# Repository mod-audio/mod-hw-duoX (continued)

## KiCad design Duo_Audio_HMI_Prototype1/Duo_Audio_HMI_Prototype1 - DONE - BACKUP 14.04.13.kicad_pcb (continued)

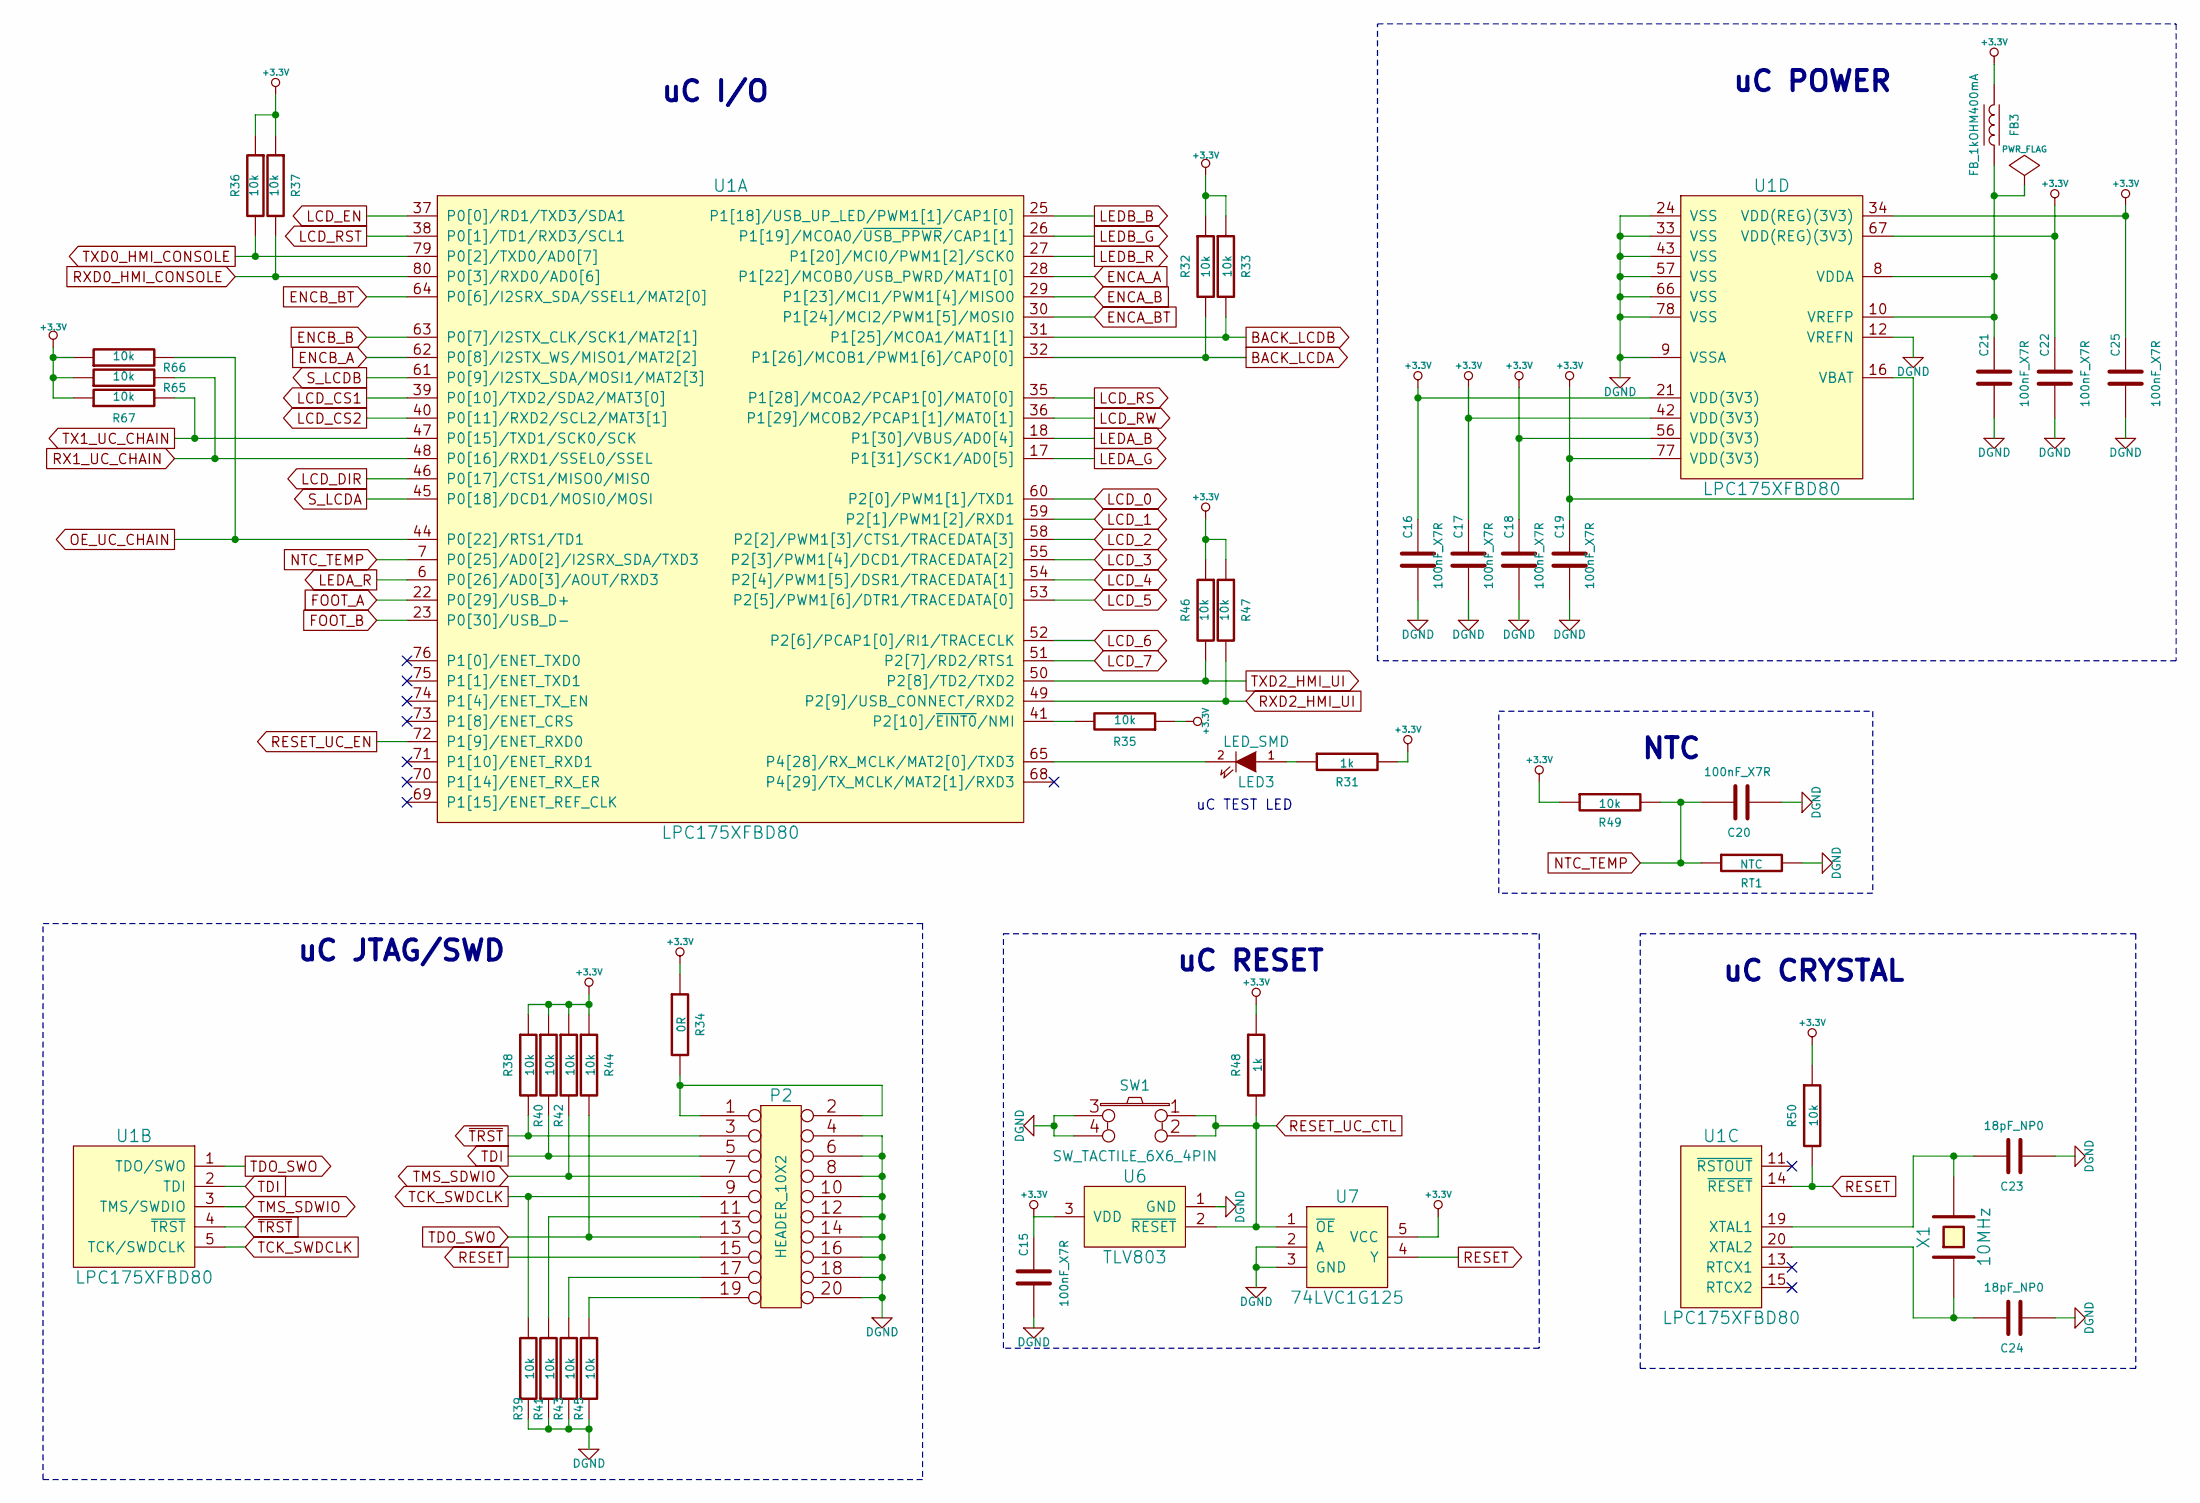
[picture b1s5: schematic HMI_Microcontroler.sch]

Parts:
C15, C16, C17, C18, C19, C20, C21, C22, C25: 100nF_X7R; SM0603
C23, C24: 18pF_NP0; SM0603
FB3: FB_1kOHM400mA; SM0805
LED3: LED_SMD; SM0805
P2: HEADER_10X2; PIN_ARRAY_2X10
R31, R48: 1k; SM0603
R32, R33, R35, R36, R37, R38, R39, R40, R41, R42, R43, R44, R45, R46, R47, R49, R50, R65, R66, R67: 10k; SM0603
R34: 0R; SM0805
RT1: NTC; SM0805
SW1: SW_TACTILE_6X6_4PIN; TACTILE_SWITCH_6x6
U1: LPC175XFBD80; LQFP80
U6: TLV803; SOT23
U7: 74LVC1G125; SOT353
X1: 10MHz; HC_49US

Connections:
+3.3V: C15.1, C16.1, C17.1, C18.1, C19.1, C22.1, C25.1, FB3.1, R31.2, R32.1, R33.1, R34.1, R35.1, R36.1, R37.1, R38.1, R40.1, R42.1, R44.1, R46.1, R47.1, R48.1, R49.1, R50.1, R65.1, R66.1, R67.1, U1.16 (VBAT), U1.21 (VDD(3V3)), U1.34 (VDD(REG)(3V3)), U1.42 (VDD(3V3)), U1.56 (VDD(3V3)), U1.67 (VDD(REG)(3V3)), U1.77 (VDD(3V3)), U6.3 (VDD), U7.5 (VCC); also elsewhere on the board
AGND: C15.2, C16.2, C17.2, C18.2, C19.2, C20.2, C21.2, C22.2, C23.2, C24.2, C25.2, P2.4, P2.6, P2.8, P2.10, P2.12, P2.14, P2.16, P2.18, P2.20, R39.1, R41.1, R43.1, R45.1, RT1.2, SW1.3, SW1.4, U1.9 (VSSA), U1.12 (VREFN), U1.24 (VSS), U1.33 (VSS), U1.43 (VSS), U1.57 (VSS), U1.66 (VSS), U1.78 (VSS), U6.1 (GND), U7.2 (A), U7.3 (GND); also elsewhere on the board
BACK_LCDA: R32.2, U1.32 (P1[26]/MCOB1/PWM1[6]/CAP0[0]); also elsewhere on the board
BACK_LCDB: R33.2, U1.31 (P1[25]/MCOA1/MAT1[1]); also elsewhere on the board
ENCA_A: U1.28 (P1[22]/MCOB0/USB_PWRD/MAT1[0]); also elsewhere on the board
ENCA_B: U1.29 (P1[23]/MCI1/PWM1[4]/MISO0); also elsewhere on the board
ENCA_BT: U1.30 (P1[24]/MCI2/PWM1[5]/MOSI0); also elsewhere on the board
ENCB_A: U1.62 (P0[8]/I2STX_WS/MISO1/MAT2[2]); also elsewhere on the board
ENCB_B: U1.63 (P0[7]/I2STX_CLK/SCK1/MAT2[1]); also elsewhere on the board
ENCB_BT: U1.64 (P0[6]/I2SRX_SDA/SSEL1/MAT2[0]); also elsewhere on the board
FOOT_A: U1.22 (P0[29]/USB_D+); also elsewhere on the board
FOOT_B: U1.23 (P0[30]/USB_D-); also elsewhere on the board
LCD_0: U1.60 (P2[0]/PWM1[1]/TXD1); also elsewhere on the board
LCD_1: U1.59 (P2[1]/PWM1[2]/RXD1); also elsewhere on the board
LCD_2: U1.58 (P2[2]/PWM1[3]/CTS1/TRACEDATA[3]); also elsewhere on the board
LCD_3: U1.55 (P2[3]/PWM1[4]/DCD1/TRACEDATA[2]); also elsewhere on the board
LCD_4: U1.54 (P2[4]/PWM1[5]/DSR1/TRACEDATA[1]); also elsewhere on the board
LCD_5: U1.53 (P2[5]/PWM1[6]/DTR1/TRACEDATA[0]); also elsewhere on the board
LCD_6: U1.52 (P2[6]/PCAP1[0]/RI1/TRACECLK); also elsewhere on the board
LCD_7: U1.51 (P2[7]/RD2/RTS1); also elsewhere on the board
LCD_CS1: U1.39 (P0[10]/TXD2/SDA2/MAT3[0]); also elsewhere on the board
LCD_CS2: U1.40 (P0[11]/RXD2/SCL2/MAT3[1]); also elsewhere on the board
LCD_DIR: U1.46 (P0[17]/CTS1/MISO0/MISO); also elsewhere on the board
LCD_EN: U1.37 (P0[0]/RD1/TXD3/SDA1); also elsewhere on the board
LCD_RS: U1.35 (P1[28]/MCOA2/PCAP1[0]/MAT0[0]); also elsewhere on the board
LCD_RST: U1.38 (P0[1]/TD1/RXD3/SCL1); also elsewhere on the board
LCD_RW: U1.36 (P1[29]/MCOB2/PCAP1[1]/MAT0[1]); also elsewhere on the board
LEDA_B: U1.18 (P1[30]/VBUS/AD0[4]); also elsewhere on the board
LEDA_G: U1.17 (P1[31]/SCK1/AD0[5]); also elsewhere on the board
LEDA_R: U1.6 (P0[26]/AD0[3]/AOUT/RXD3); also elsewhere on the board
LEDB_B: U1.25 (P1[18]/USB_UP_LED/PWM1[1]/CAP1[0]); also elsewhere on the board
LEDB_G: U1.26 (P1[19]/MCOA0/~USB_PPWR~/CAP1[1]); also elsewhere on the board
LEDB_R: U1.27 (P1[20]/MCI0/PWM1[2]/SCK0); also elsewhere on the board
unnamed: LED3.1 (A), R31.1
unnamed: LED3.2 (K), U1.65 (P4[28]/RX_MCLK/MAT2[0]/TXD3)
unnamed: R35.2, U1.41 (P2[10]/~EINT0~/NMI)
unnamed: C21.1, FB3.2, U1.8 (VDDA), U1.10 (VREFP)
unnamed: C23.1, U1.19 (XTAL1), X1.2
unnamed: C24.1, U1.20 (XTAL2), X1.1
unnamed: P2.11, R41.2
unnamed: P2.1, P2.2, R34.2
unnamed: P2.17, R43.2
unnamed: P2.19, R45.2
NTC_TEMP: C20.1, R49.2, RT1.1, U1.7 (P0[25]/AD0[2]/I2SRX_SDA/TXD3)
OE_UC_CHAIN: R66.2, U1.44 (P0[22]/RTS1/TD1); also elsewhere on the board
RESET: P2.15, R50.2, U1.14 (~RESET), U7.4 (Y)
RESET_UC_CTL: R48.2, SW1.1, SW1.2, U6.2 (~RESET), U7.1 (~OE); also elsewhere on the board
RESET_UC_EN: U1.72 (P1[9]/ENET_RXD0); also elsewhere on the board
RX1_UC_CHAIN: R65.2, U1.48 (P0[16]/RXD1/SSEL0/SSEL); also elsewhere on the board
RXD0_HMI_CONSOLE: R37.2, U1.80 (P0[3]/RXD0/AD0[6]); also elsewhere on the board
RXD2_HMI_UI: R47.2, U1.49 (P2[9]/USB_CONNECT/RXD2); also elsewhere on the board
S_LCDA: U1.45 (P0[18]/DCD1/MOSI0/MOSI); also elsewhere on the board
S_LCDB: U1.61 (P0[9]/I2STX_SDA/MOSI1/MAT2[3]); also elsewhere on the board
TCK_SWDCLK: P2.9, R39.2, U1.5 (TCK/SWDCLK)
TDI: P2.5, R40.2, U1.2 (TDI)
TDO_SWO: P2.13, R44.2, U1.1 (TDO/SWO)
TMS_SDWIO: P2.7, R42.2, U1.3 (TMS/SWDIO)
TX1_UC_CHAIN: R67.2, U1.47 (P0[15]/TXD1/SCK0/SCK); also elsewhere on the board
TXD0_HMI_CONSOLE: R36.2, U1.79 (P0[2]/TXD0/AD0[7]); also elsewhere on the board
TXD2_HMI_UI: R46.2, U1.50 (P2[8]/TD2/TXD2); also elsewhere on the board
~TRST: P2.3, R38.2, U1.4 (~TRST)

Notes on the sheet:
uC JTAG/SWD
uC RESET
uC CRYSTAL
uC POWER
uC I/O
uC TEST LED
NTC

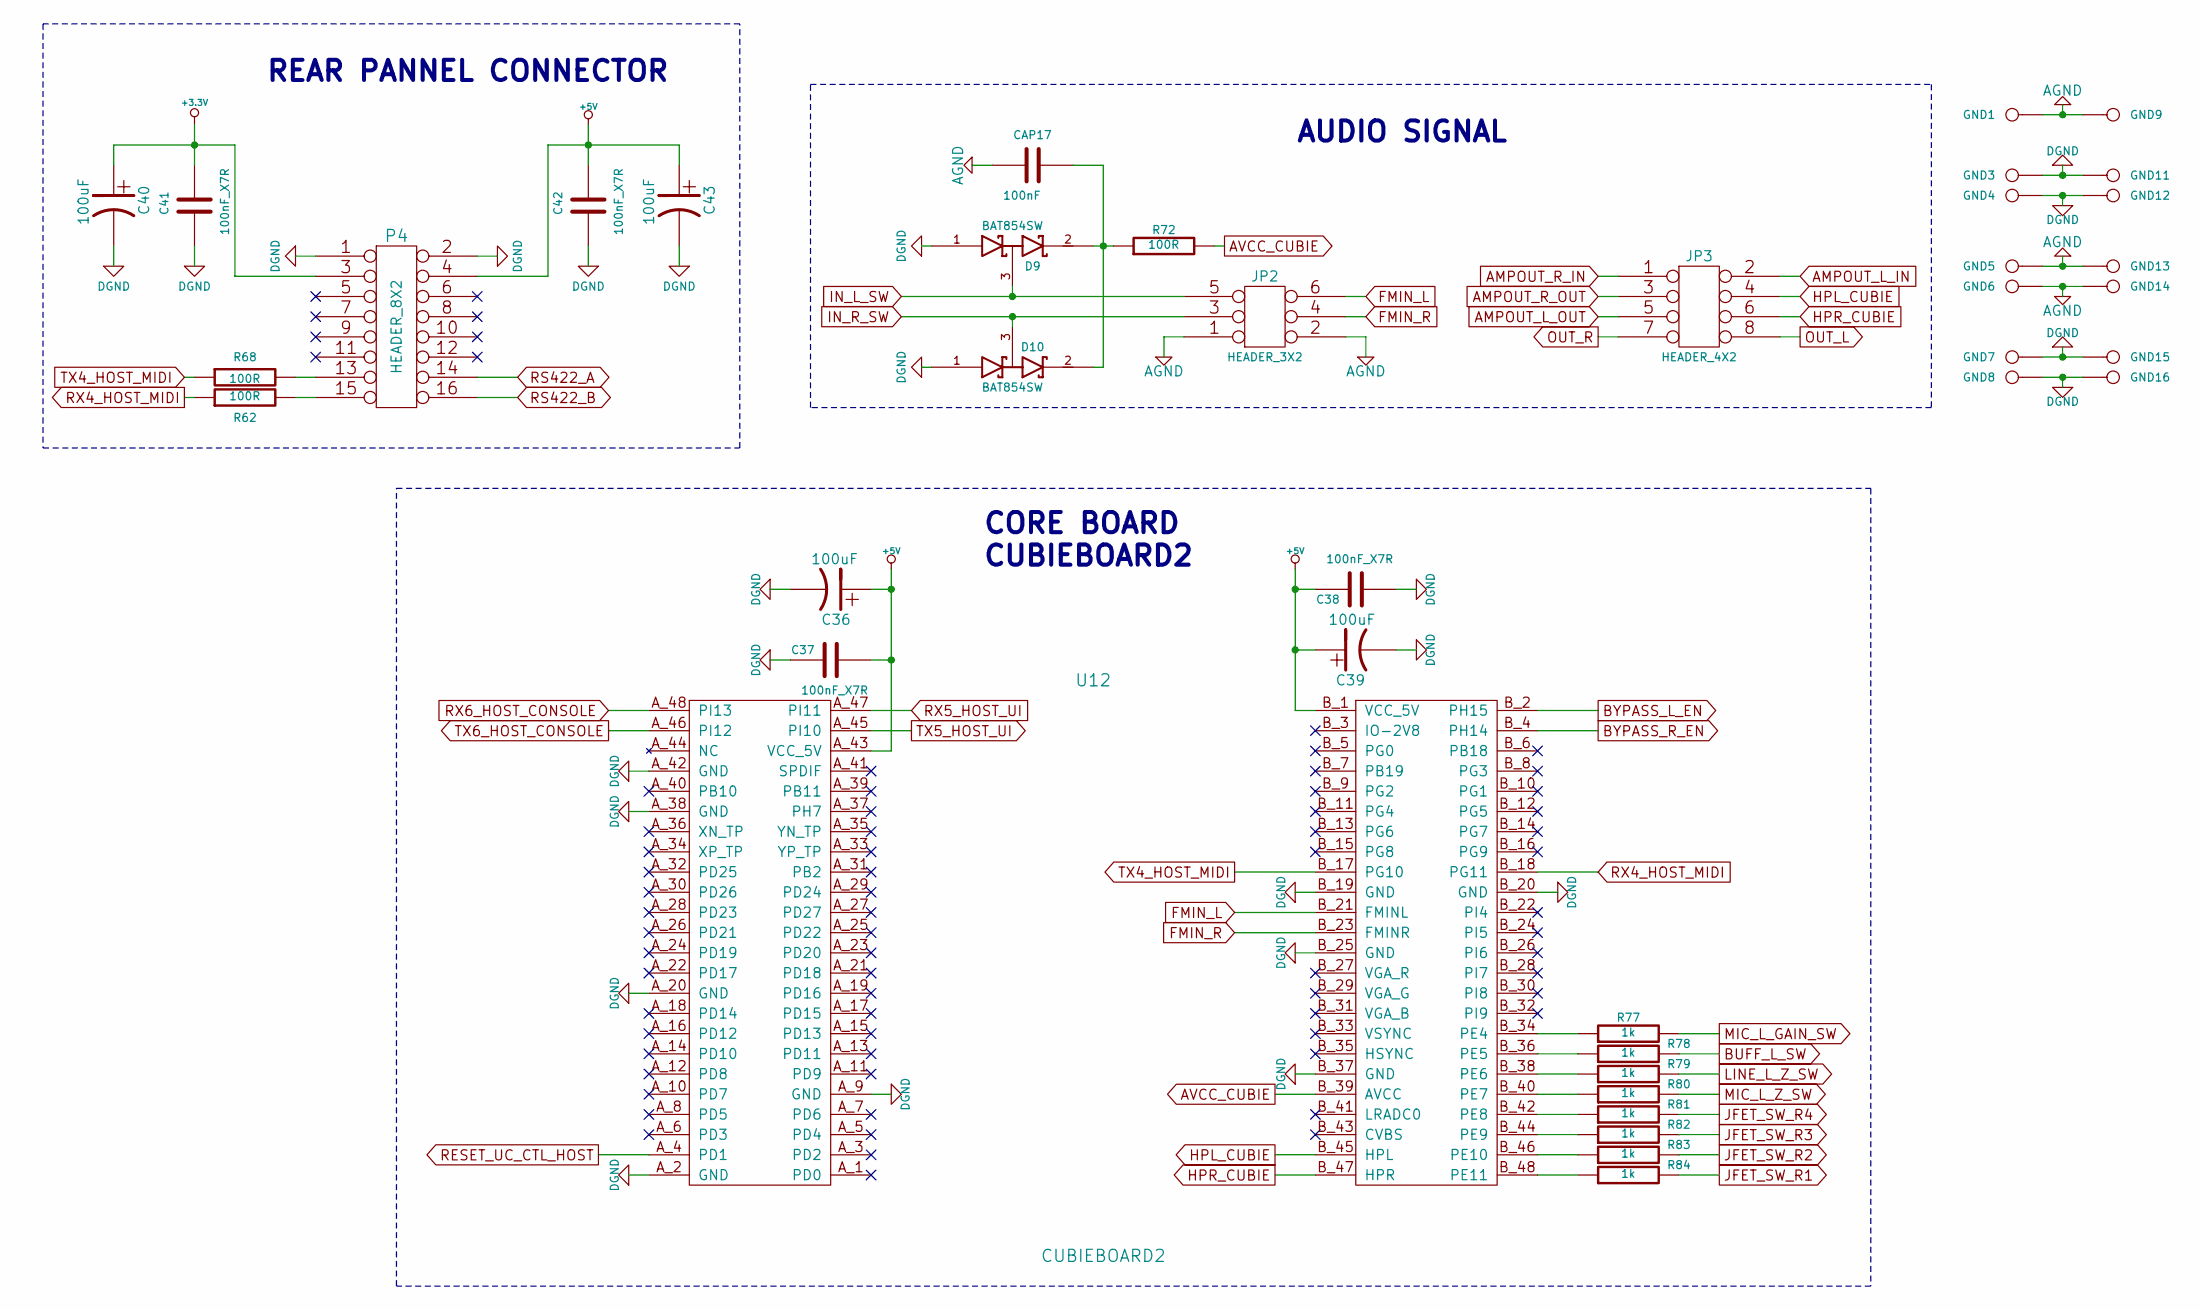
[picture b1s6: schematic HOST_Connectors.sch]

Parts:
C36, C39, C40, C43: 100uF; CAP_RAD_5MM
C37, C38, C41, C42: 100nF_X7R; SM0603
CAP17: 100nF; SM0603
D9, D10: BAT854SW; SOT323
GND1, GND3, GND4, GND5, GND6, GND7, GND8, GND9, GND11, GND12, GND13, GND14, GND15, GND16: CONN_1; PAD_GND
JP2: HEADER_3X2; PIN_ARRAY_3X2
JP3: HEADER_4X2; PIN_ARRAY_4X2
P4: HEADER_8X2; pin_array_8x2
R62, R68: 100R; SM0805
R72: 100R; RES_PTH_6MM
R77, R78, R79, R80, R81, R82, R83, R84: 1k; SM0603
U12: CUBIEBOARD2

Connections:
+3.3V: C40.1, C41.1, P4.3; also elsewhere on the board
+5V: C36.1, C37.1, C38.2, C39.1, C42.1, C43.1, P4.4, U12.A_43 (VCC_5V), U12.B_1 (VCC_5V); also elsewhere on the board
AGND: C36.2, C37.2, C38.1, C39.2, C40.2, C41.2, C42.2, C43.2, CAP17.2, D9.1 (Anode), D10.1 (Anode), GND1.1, GND3.1, GND4.1, GND5.1, GND6.1, GND7.1, GND8.1, GND9.1, GND11.1, GND12.1, GND13.1, GND14.1, GND15.1, GND16.1, JP2.1, JP2.2, P4.1, P4.2, U12.A_2 (GND), U12.A_9 (GND), U12.A_20 (GND), U12.A_38 (GND), U12.A_42 (GND), U12.B_19 (GND), U12.B_20 (GND), U12.B_25 (GND), U12.B_37 (GND); also elsewhere on the board
AMPOUT_L_IN: JP3.2; also elsewhere on the board
AMPOUT_L_OUT: JP3.5; also elsewhere on the board
AMPOUT_R_IN: JP3.1; also elsewhere on the board
AMPOUT_R_OUT: JP3.3; also elsewhere on the board
AVCC_CUBIE: R72.2, U12.B_39 (AVCC)
BUFF_L_SW: R78.2; also elsewhere on the board
BYPASS_L_EN: U12.B_2 (PH15); also elsewhere on the board
BYPASS_R_EN: U12.B_4 (PH14); also elsewhere on the board
FMIN_L: JP2.6, U12.B_21 (FMINL)
FMIN_R: JP2.4, U12.B_23 (FMINR)
HPL_CUBIE: JP3.4, U12.B_45 (HPL)
HPR_CUBIE: JP3.6, U12.B_47 (HPR)
IN_L_SW: D9.3 (AK), JP2.5; also elsewhere on the board
IN_R_SW: D10.3 (AK), JP2.3; also elsewhere on the board
JFET_SW_R1: R84.2; also elsewhere on the board
JFET_SW_R2: R83.2; also elsewhere on the board
JFET_SW_R3: R82.2; also elsewhere on the board
JFET_SW_R4: R81.2; also elsewhere on the board
LINE_L_Z_SW: R79.2; also elsewhere on the board
MIC_L_GAIN_SW: R77.2; also elsewhere on the board
MIC_L_Z_SW: R80.2; also elsewhere on the board
unnamed: P4.13, R68.2
unnamed: P4.15, R62.2
unnamed: R81.1, U12.B_42 (PE8)
unnamed: R82.1, U12.B_44 (PE9)
unnamed: R83.1, U12.B_46 (PE10)
unnamed: R84.1, U12.B_48 (PE11)
unnamed: R77.1, U12.B_34 (PE4)
unnamed: R78.1, U12.B_36 (PE5)
unnamed: R79.1, U12.B_38 (PE6)
unnamed: R80.1, U12.B_40 (PE7)
unnamed: CAP17.1, D9.2 (cathode), D10.2 (cathode), R72.1
OUT_L: JP3.8; also elsewhere on the board
OUT_R: JP3.7; also elsewhere on the board
RESET_UC_CTL_HOST: U12.A_4 (PD1); also elsewhere on the board
RS422_A: P4.14; also elsewhere on the board
RS422_B: P4.16; also elsewhere on the board
RX4_HOST_MIDI: R62.1, U12.B_18 (PG11)
RX5_HOST_UI: U12.A_47 (PI11); also elsewhere on the board
RX6_HOST_CONSOLE: U12.A_48 (PI13); also elsewhere on the board
TX4_HOST_MIDI: R68.1, U12.B_17 (PG10)
TX5_HOST_UI: U12.A_45 (PI10); also elsewhere on the board
TX6_HOST_CONSOLE: U12.A_46 (PI12); also elsewhere on the board

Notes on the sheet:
CORE BOARD CUBIEBOARD2
REAR PANNEL CONNECTOR
AUDIO SIGNAL

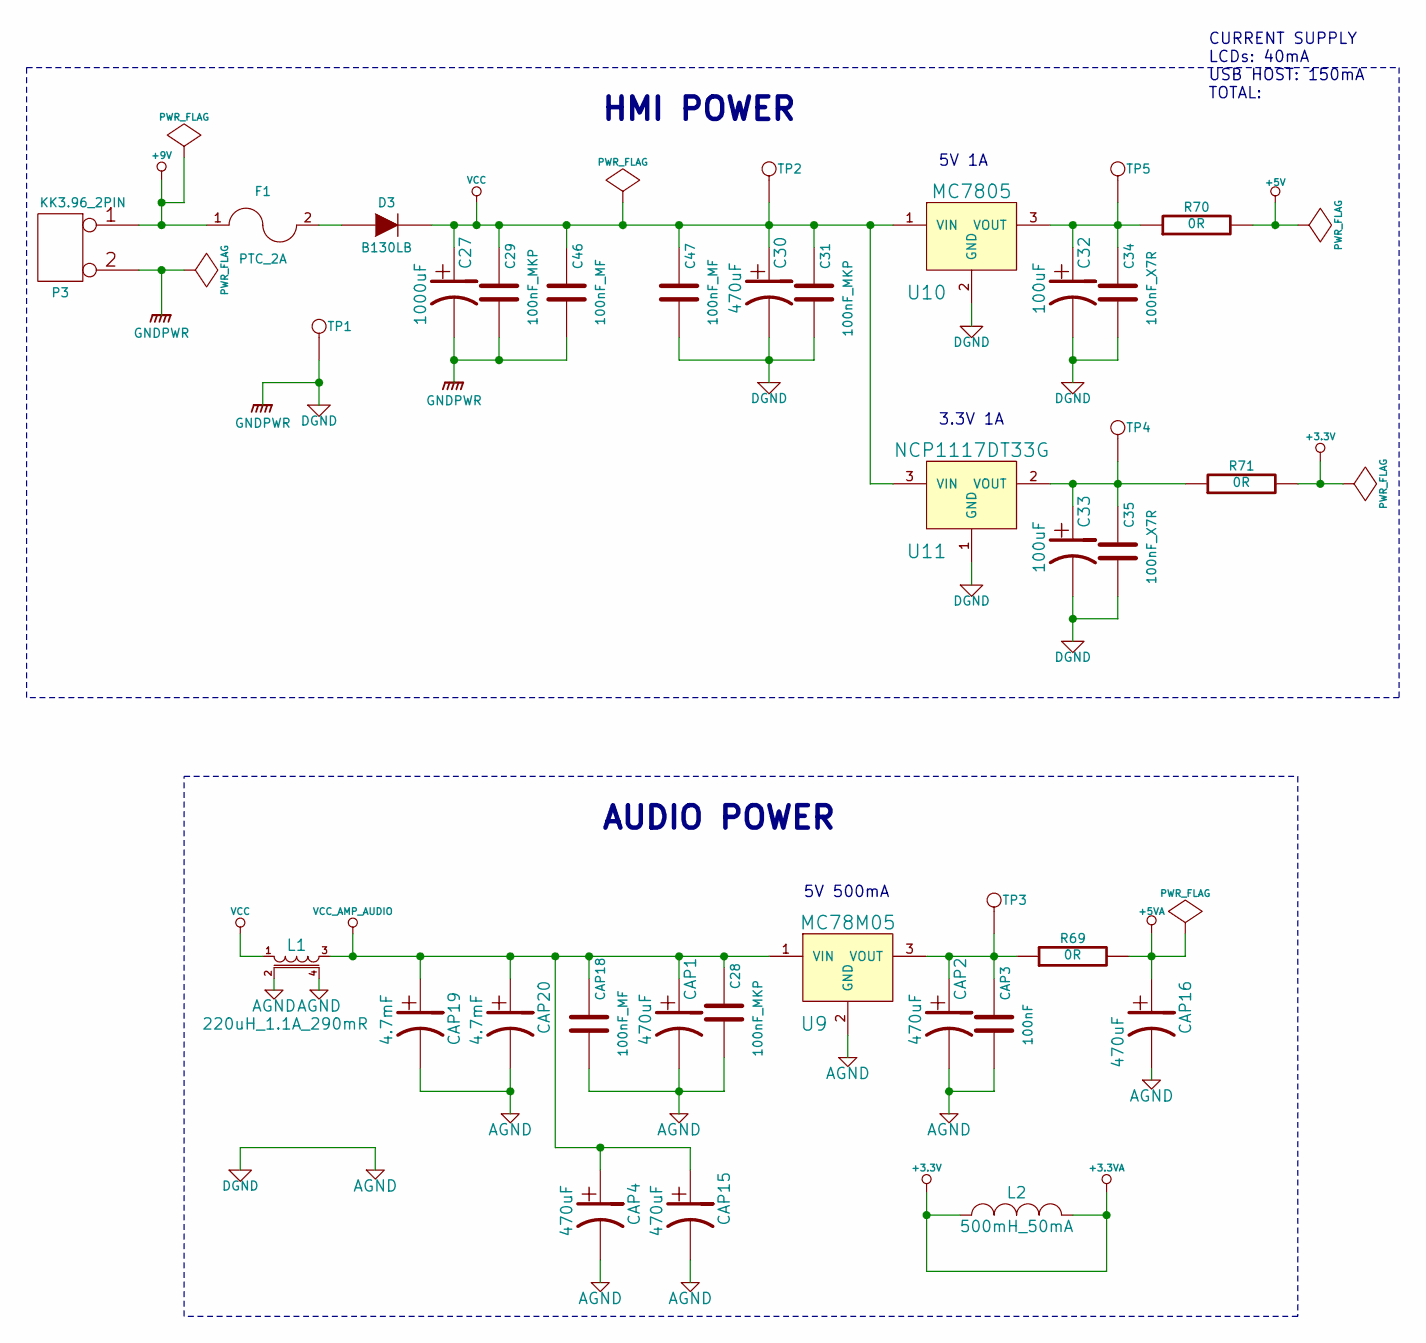
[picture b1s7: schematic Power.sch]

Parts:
C27: 1000uF; CAP_RAD_10MM
C28, C29, C31: 100nF_MKP; CAP_FILM_18X5_L15
C30: 470uF; CAP_RAD_8MM
C32, C33: 100uF; CAP_RAD_5MM
C34, C35: 100nF_X7R; SM0603
C46, C47: 100nF_MF; CAP_FILM_12.6X4.5_L10
CAP1, CAP2, CAP4, CAP15, CAP16: 470uF; CAP_RAD_8MM
CAP3: 100nF; SM0603
CAP18: 100nF_MF; CAP_FILM_12.6X4.5_L10
CAP19, CAP20: 4.7mF; CAP_RAD_16MM
D3: B130LB; DO-214AA(SMB)
F1: PTC_2A; SM2920
L1: 220uH_1.1A_290mR; IND_RAD_10MM_4P
L2: 500mH_50mA; IND_RAD_10MM_4P
P3: KK3.96_2PIN
R69, R70, R71: 0R; SM0805
TP1, TP2, TP3, TP4, TP5: CONN_1; SIL-1
U9: MC78M05; DPAK(369C)
U10: MC7805; DPAK(369C)
U11: NCP1117DT33G; DPAK(369C)

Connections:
+3.3V: L2.1, L2.2, R71.2; also elsewhere on the board
+5V: R70.2; also elsewhere on the board
+5VA: CAP16.1, R69.2; also elsewhere on the board
+9V: F1.1, P3.1
AGND: C27.2, C28.2, C29.2, C30.2, C31.2, C32.2, C33.2, C34.2, C35.2, C46.2, C47.2, CAP1.2, CAP2.2, CAP3.2, CAP4.2, CAP15.2, CAP16.2, CAP18.2, CAP19.2, CAP20.2, L1.2, L1.4, P3.2 (PM), TP1.1, U9.2 (GND), U10.2 (GND), U11.1 (GND); also elsewhere on the board
unnamed: C33.1, C35.1, R71.1, TP4.1, U11.2 (VOUT)
unnamed: D3.1 (A), F1.2
unnamed: CAP2.1, CAP3.1, R69.1, TP3.1, U9.3 (VOUT)
unnamed: C32.1, C34.1, R70.1, TP5.1, U10.3 (VOUT)
VCC: C27.1, C29.1, C30.1, C31.1, C46.1, C47.1, D3.2 (K), L1.1, TP2.1, U10.1 (VIN), U11.3 (VIN)
VCC_AMP_AUDIO: C28.1, CAP1.1, CAP4.1, CAP15.1, CAP18.1, CAP19.1, CAP20.1, L1.3, U9.1 (VIN); also elsewhere on the board

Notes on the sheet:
HMI POWER
AUDIO POWER
CURRENT SUPPLY LCDs: 40mA USB HOST: 150mA TOTAL:
5V 500mA
5V 1A
3.3V 1A

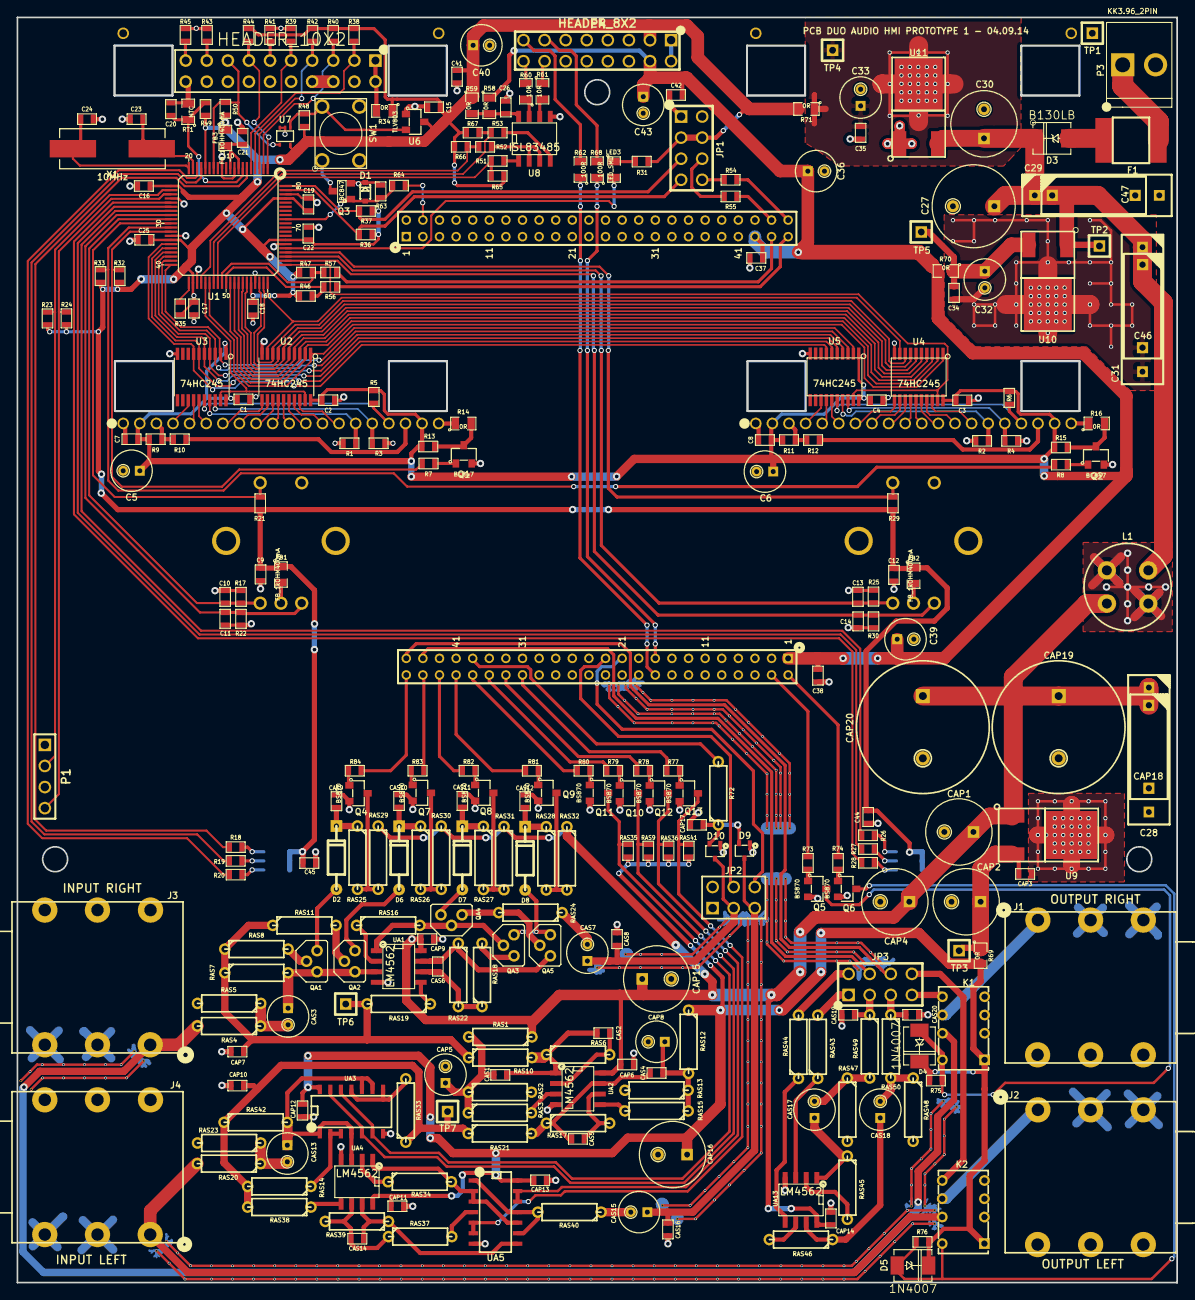
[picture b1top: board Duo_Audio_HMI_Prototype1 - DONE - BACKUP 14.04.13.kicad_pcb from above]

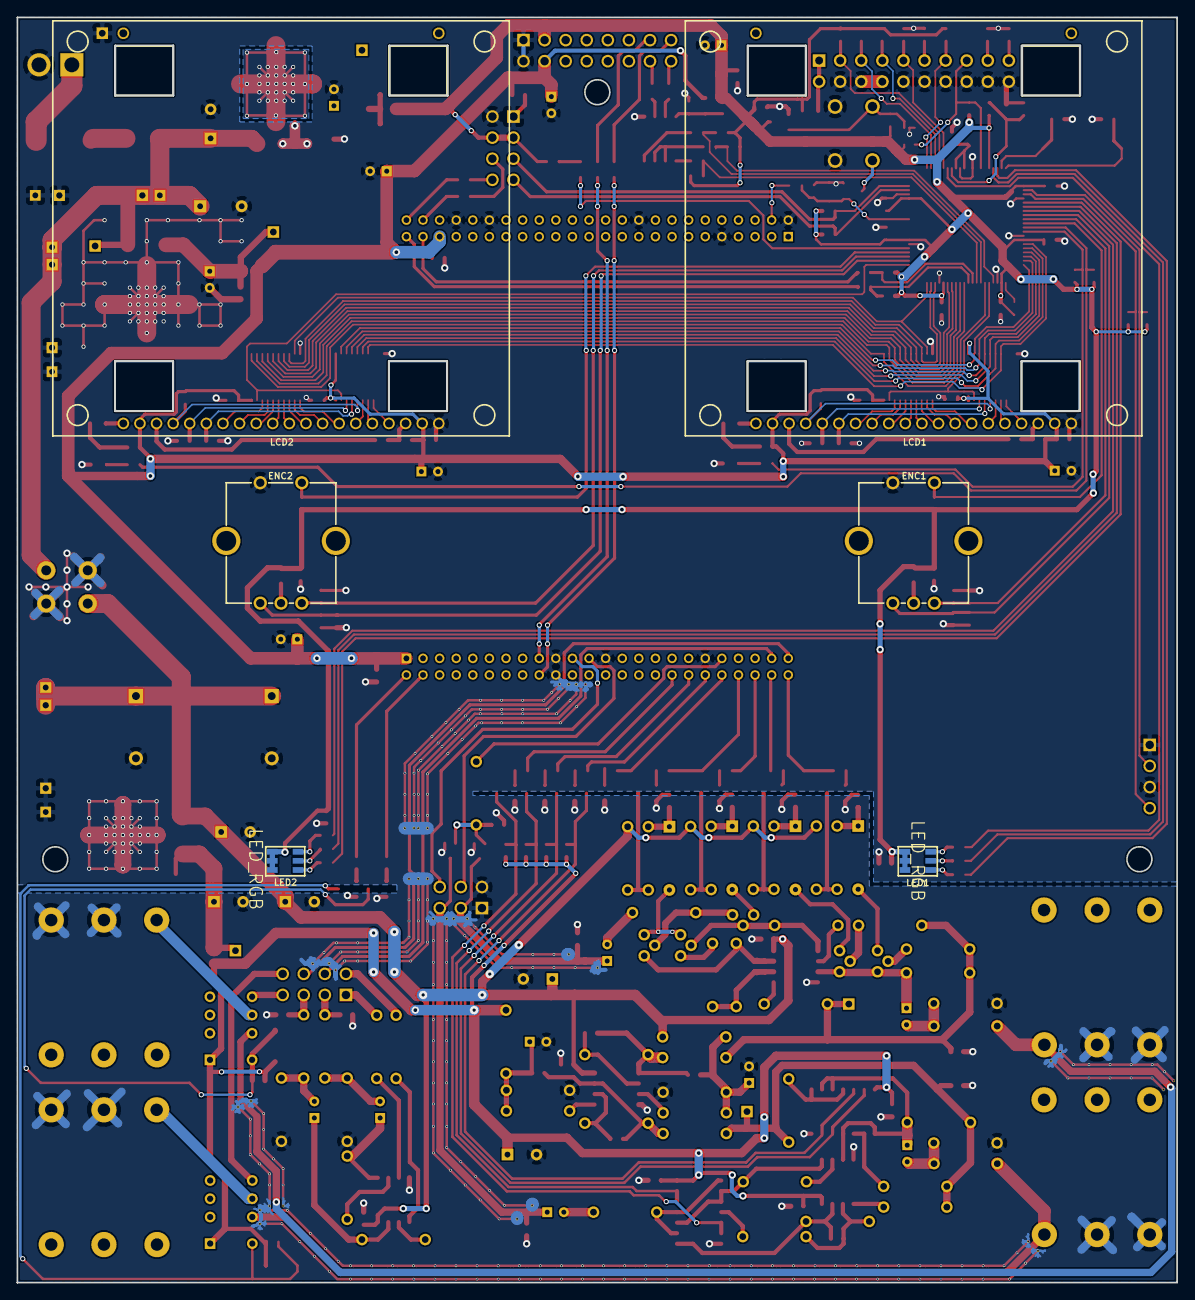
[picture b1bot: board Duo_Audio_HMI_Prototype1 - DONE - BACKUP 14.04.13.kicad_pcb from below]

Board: 2 copper layers, 139.7 x 152.4 mm, 336 parts (6 on the bottom side), 233 nets.
